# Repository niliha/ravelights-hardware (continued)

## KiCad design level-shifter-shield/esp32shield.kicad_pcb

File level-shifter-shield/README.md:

#  ESP32-DevKitC Level Shifter Shield

A shield for the ESP32-DevKitC allowing 3.3V to 5V/12V level shifting of 8 outputs, allowing to drive WS28XX LEDs at a distance of up to 50 meters.

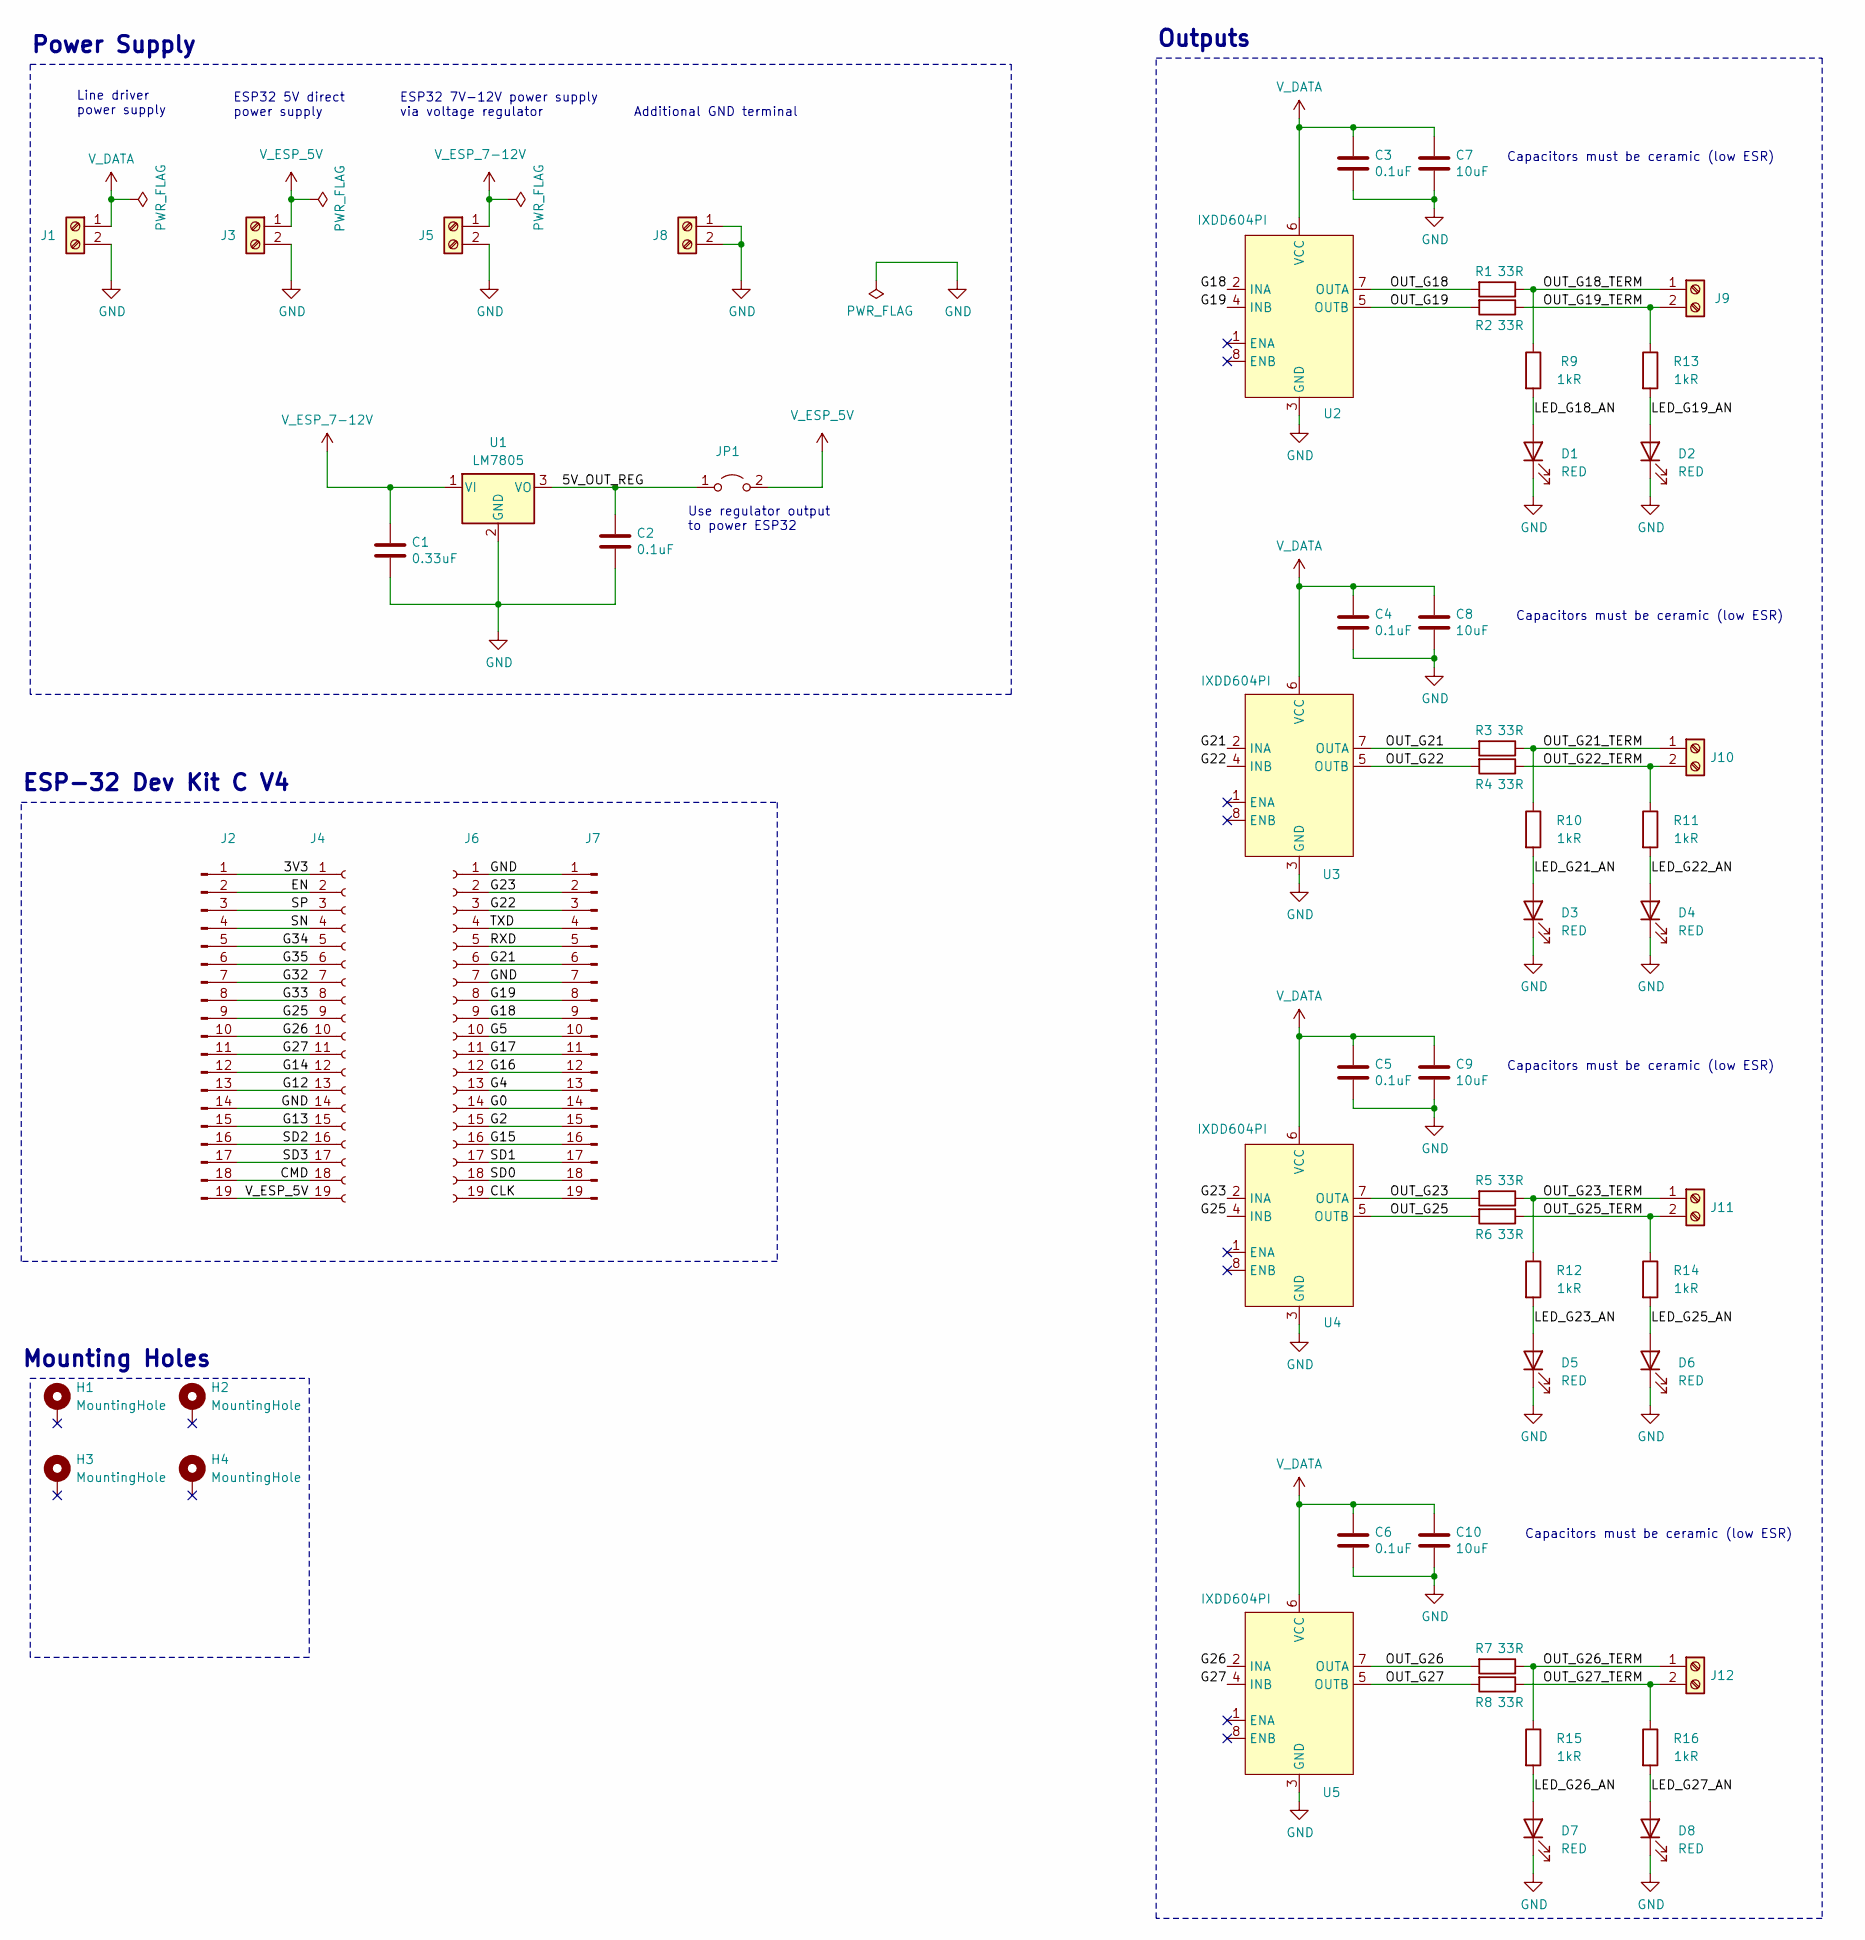
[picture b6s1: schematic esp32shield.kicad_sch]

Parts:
C1: 0.33uF; C_Disc_D3.0mm_W1.6mm_P2.50mm
C2, C3, C4, C5, C6: 0.1uF; C_Disc_D3.0mm_W1.6mm_P2.50mm
C7, C8, C9, C10: 10uF; C_Disc_D4.7mm_W2.5mm_P5.00mm
D1, D2, D3, D4, D5, D6, D7, D8: RED; LED_D3.0mm
H1, H2, H3, H4: MountingHole; MountingHole_2.2mm_M2_Pad
J1, J3, J5, J8: Power_Terminal; TerminalBlock_Phoenix_MKDS-1,5-2-5.08_1x02_P5.08mm_Horizont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
J2, J7: Conn_01x19_Pin; PinHeader_1x19_P2.54mm_Vertical
J4, J6: Conn_01x19_Socket; PinSocket_1x19_P2.54mm_Vertical
J9, J10, J11, J12: Screw_Terminal_01x02; TerminalBlock_Phoenix_MKDS-1,5-2-5.08_1x02_P5.08mm_Horizont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
JP1: Jumper_2_Open; PinHeader_1x02_P2.54mm_Vertical
R1, R2, R3, R4, R5, R6, R7, R8: 33R; R_Axial_DIN0207_L6.3mm_D2.5mm_P2.54mm_Vertical
R9, R10, R11, R12, R13, R14, R15, R16: 1kR; R_Axial_DIN0207_L6.3mm_D2.5mm_P2.54mm_Vertical
U1: LM7805; TO-220-3_Vertical
U2, U3, U4, U5: IXDD604PI; DIP-8_W7.62mm_Socket

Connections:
/3V3: J2.1, J4.1
/5V_OUT_REG: C2.1, JP1.1 (A), U1.3 (VO)
/CLK: J6.19, J7.19
/CMD: J2.18, J4.18
/EN: J2.2, J4.2
/G0: J6.14, J7.14
/G2: J6.15, J7.15
/G4: J6.13, J7.13
/G5: J6.10, J7.10
/G12: J2.13, J4.13
/G13: J2.15, J4.15
/G14: J2.12, J4.12
/G15: J6.16, J7.16
/G16: J6.12, J7.12
/G17: J6.11, J7.11
/G18: J6.9, J7.9, U2.2 (INA)
/G19: J6.8, J7.8, U2.4 (INB)
/G21: J6.6, J7.6, U3.2 (INA)
/G22: J6.3, J7.3, U3.4 (INB)
/G23: J6.2, J7.2, U4.2 (INA)
/G25: J2.9, J4.9, U4.4 (INB)
/G26: J2.10, J4.10, U5.2 (INA)
/G27: J2.11, J4.11, U5.4 (INB)
/G32: J2.7, J4.7
/G33: J2.8, J4.8
/G34: J2.5, J4.5
/G35: J2.6, J4.6
/LED_G18_AN: D1.2 (A), R9.2
/LED_G19_AN: D2.2 (A), R13.2
/LED_G21_AN: D3.2 (A), R10.2
/LED_G22_AN: D4.2 (A), R11.2
/LED_G23_AN: D5.2 (A), R12.2
/LED_G25_AN: D6.2 (A), R14.2
/LED_G26_AN: D7.2 (A), R15.2
/LED_G27_AN: D8.2 (A), R16.2
/OUT_G18: R1.2, U2.7 (OUTA)
/OUT_G18_TERM: J9.1, R1.1, R9.1
/OUT_G19: R2.2, U2.5 (OUTB)
/OUT_G19_TERM: J9.2, R2.1, R13.1
/OUT_G21: R3.2, U3.7 (OUTA)
/OUT_G21_TERM: J10.1, R3.1, R10.1
/OUT_G22: R4.2, U3.5 (OUTB)
/OUT_G22_TERM: J10.2, R4.1, R11.1
/OUT_G23: R5.2, U4.7 (OUTA)
/OUT_G23_TERM: J11.1, R5.1, R12.1
/OUT_G25: R6.2, U4.5 (OUTB)
/OUT_G25_TERM: J11.2, R6.1, R14.1
/OUT_G26: R7.2, U5.7 (OUTA)
/OUT_G26_TERM: J12.1, R7.1, R15.1
/OUT_G27: R8.2, U5.5 (OUTB)
/OUT_G27_TERM: J12.2, R8.1, R16.1
/RXD: J6.5, J7.5
/SD0: J6.18, J7.18
/SD1: J6.17, J7.17
/SD2: J2.16, J4.16
/SD3: J2.17, J4.17
/SN: J2.4, J4.4
/SP: J2.3, J4.3
/TXD: J6.4, J7.4
GND: C1.2, C2.2, C3.2, C4.2, C5.2, C6.2, C7.2, C8.2, C9.2, C10.2, D1.1 (K), D2.1 (K), D3.1 (K), D4.1 (K), D5.1 (K), D6.1 (K), D7.1 (K), D8.1 (K), J1.2, J2.14, J3.2, J4.14, J5.2, J6.1, J6.7, J7.1, J7.7, J8.1, J8.2, U1.2 (GND), U2.3 (GND), U3.3 (GND), U4.3 (GND), U5.3 (GND)
V_DATA: C3.1, C4.1, C5.1, C6.1, C7.1, C8.1, C9.1, C10.1, J1.1, U2.6 (VCC), U3.6 (VCC), U4.6 (VCC), U5.6 (VCC)
V_ESP_5V: J2.19, J3.1, J4.19, JP1.2 (B)
V_ESP_7-12V: C1.1, J5.1, U1.1 (VI)

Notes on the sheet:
Use regulator output to power ESP32
Additional GND terminal
Capacitors must be ceramic (low ESR)
Outputs
Line driver power supply
ESP32 7V-12V power supply via voltage regulator
ESP32 5V direct power supply
ESP-32 Dev Kit C V4
Power Supply
Mounting Holes

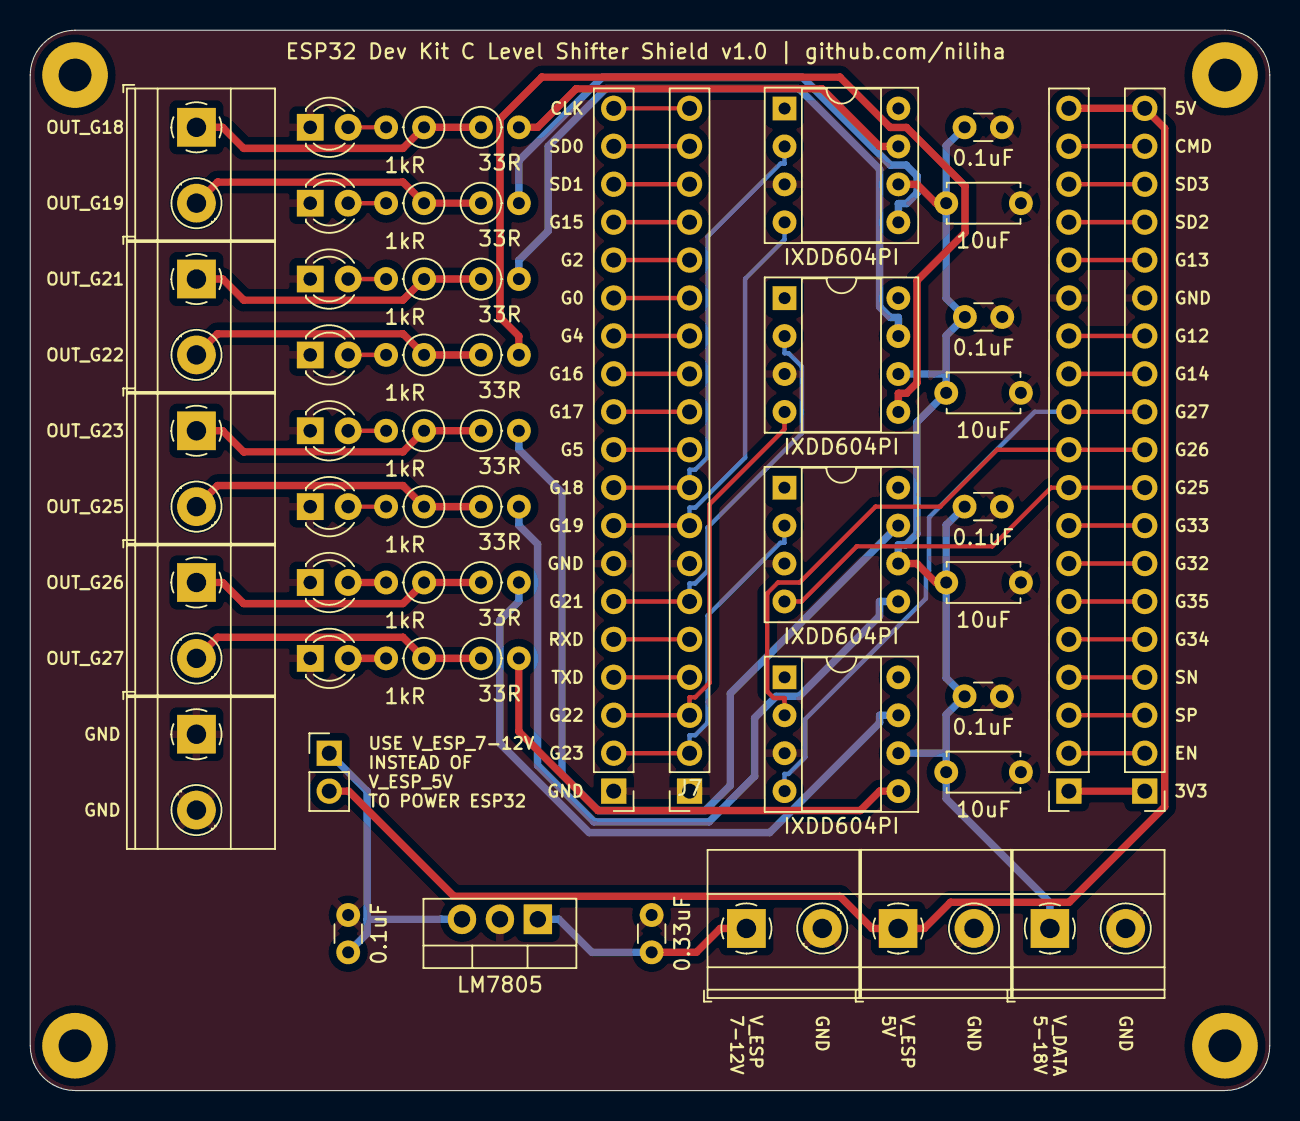
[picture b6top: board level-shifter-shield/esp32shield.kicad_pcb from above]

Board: 2 copper layers, 83.0 x 71.0 mm, 56 parts (0 on the bottom side), 63 nets.

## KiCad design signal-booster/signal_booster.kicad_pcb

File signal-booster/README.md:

# WS28XX Signal Booster

Allows to transmit up to 2 WS28XX data signals over long distances (up to 50m when GND and DATA are close together) while protecting the microcontroller pin or LED chip from sourcing too much current.
This PCB embeds an `IXDD604PI` gate driver IC acting as high-current line driver.
Further details can be derived from the [datasheet](https://ixapps.ixys.com/DataSheet/IXD_604.pdf).

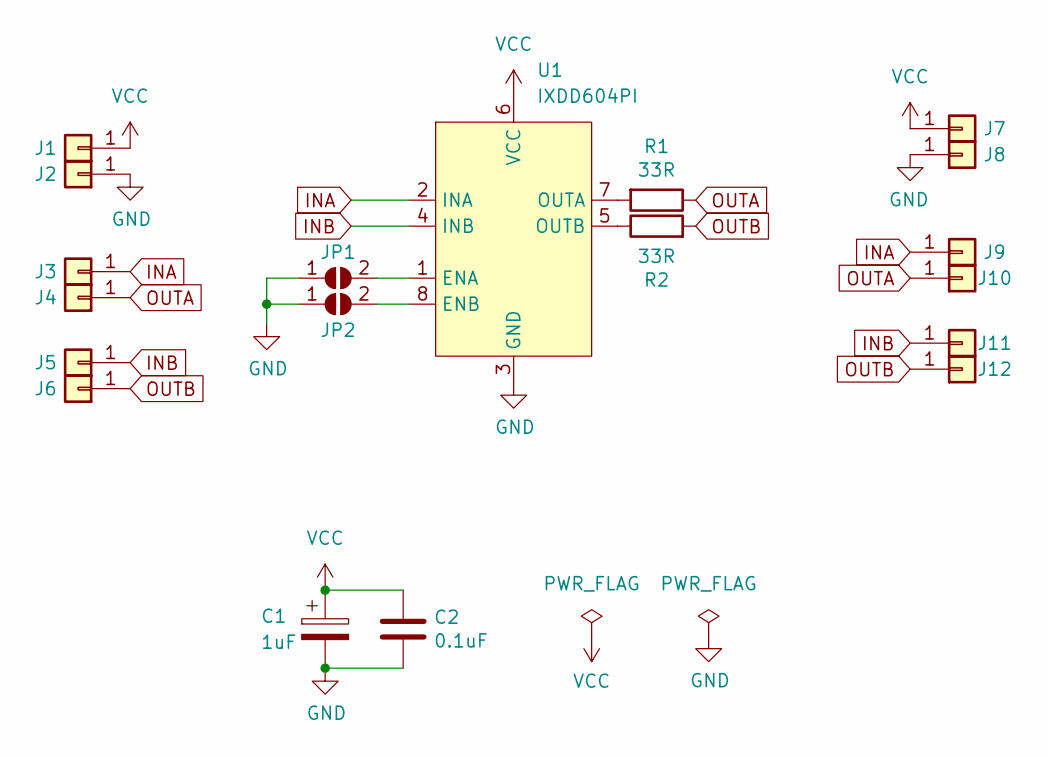
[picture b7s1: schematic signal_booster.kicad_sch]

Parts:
C1: 1uF; CP_Radial_D4.0mm_P2.00mm
C2: 0.1uF; C_Disc_D3.0mm_W1.6mm_P2.50mm
J1, J2, J3, J4, J5, J6, J7, J8, J9, J10, J11, J12: Conn_01x01; SolderWire-0.5sqmm_1x01_D0.9mm_OD2.1mm
JP1, JP2: SolderJumper_2_Open; SolderJumper-2_P1.3mm_Open_RoundedPad1.0x1.5mm
R1, R2: 33R; R_Axial_DIN0207_L6.3mm_D2.5mm_P2.54mm_Vertical
U1: IXDD604PI; DIP-8_W7.62mm_Socket

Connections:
GND: C1.2, C2.2, J2.1, J8.1, JP1.1 (A), JP2.1 (A), U1.3 (GND)
INA: J3.1, J9.1, U1.2 (INA)
INB: J5.1, J11.1, U1.4 (INB)
unnamed: JP1.2 (B), U1.1 (ENA)
unnamed: JP2.2 (B), U1.8 (ENB)
unnamed: R1.2, U1.7 (OUTA)
unnamed: R2.1, U1.5 (OUTB)
OUTA: J4.1, J10.1, R1.1
OUTB: J6.1, J12.1, R2.2
VCC: C1.1, C2.1, J1.1, J7.1, U1.6 (VCC)

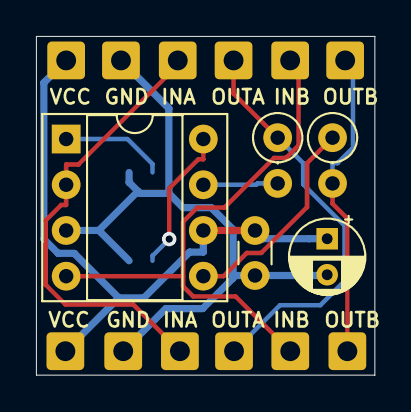
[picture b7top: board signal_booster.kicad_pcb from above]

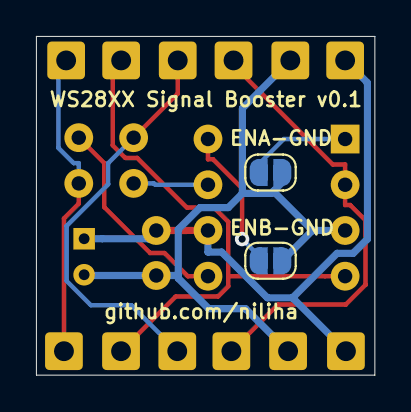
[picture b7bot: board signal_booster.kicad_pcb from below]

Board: 2 copper layers, 18.8 x 18.8 mm, 19 parts (2 on the bottom side), 10 nets.

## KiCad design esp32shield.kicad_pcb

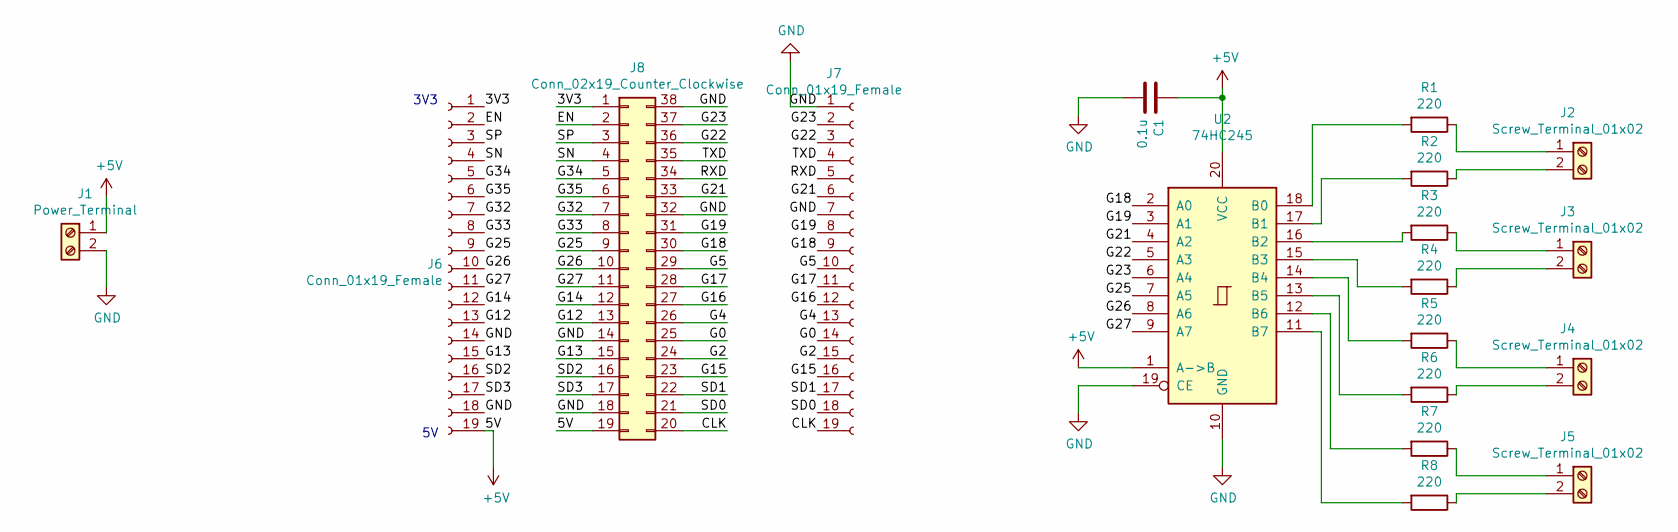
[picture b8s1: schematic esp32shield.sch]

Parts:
C1: 0.1u; C_Disc_D3.0mm_W1.6mm_P2.50mm
J1: Power_Terminal; TerminalBlock_Phoenix_MKDS-1,5-2_1x02_P5.00mm_Horizontal
J2, J3, J4, J5: Screw_Terminal_01x02; TerminalBlock_Phoenix_MKDS-1,5-2-5.08_1x02_P5.08mm_Horizont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
J6, J7: Conn_01x19_Female; PinSocket_1x19_P2.54mm_Vertical
J8: Conn_02x19_Counter_Clockwise; PinHeader_2x19_P2.54mm_Vertical
R1, R2, R3, R4, R5, R6, R7, R8: 220; R_Axial_DIN0207_L6.3mm_D2.5mm_P2.54mm_Vertical
U2: 74HC245; DIP-20_W7.62mm

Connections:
+5V: C1.1, J1.1, J6.19, J8.19, U2.1 (A->B), U2.20 (VCC)
/3V3: J6.1, J8.1
/CLK: J7.19, J8.20
/EN: J6.2, J8.2
/G0: J7.14, J8.25
/G2: J7.15, J8.24
/G4: J7.13, J8.26
/G5: J7.10, J8.29
/G12: J6.13, J8.13
/G13: J6.15, J8.15
/G14: J6.12, J8.12
/G15: J7.16, J8.23
/G16: J7.12, J8.27
/G17: J7.11, J8.28
/G18: J7.9, J8.30, U2.2 (A0)
/G19: J7.8, J8.31, U2.3 (A1)
/G21: J7.6, J8.33, U2.4 (A2)
/G22: J7.3, J8.36, U2.5 (A3)
/G23: J7.2, J8.37, U2.6 (A4)
/G25: J6.9, J8.9, U2.7 (A5)
/G26: J6.10, J8.10, U2.8 (A6)
/G27: J6.11, J8.11, U2.9 (A7)
/G32: J6.7, J8.7
/G33: J6.8, J8.8
/G34: J6.5, J8.5
/G35: J6.6, J8.6
/RXD: J7.5, J8.34
/SD0: J7.18, J8.21
/SD1: J7.17, J8.22
/SD2: J6.16, J8.16
/SD3: J6.17, J8.17
/SN: J6.4, J8.4
/SP: J6.3, J8.3
/TXD: J7.4, J8.35
GND: C1.2, J1.2, J6.14, J6.18, J7.1, J7.7, J8.14, J8.18, J8.32, J8.38, U2.10 (GND), U2.19 (CE)
unnamed: J2.1, R1.1
unnamed: J2.2, R2.1
unnamed: J3.1, R3.1
unnamed: J3.2, R4.1
unnamed: J4.1, R5.1
unnamed: J4.2, R6.1
unnamed: J5.1, R7.1
unnamed: J5.2, R8.1
unnamed: R1.2, U2.18 (B0)
unnamed: R2.2, U2.17 (B1)
unnamed: R3.2, U2.16 (B2)
unnamed: R4.2, U2.15 (B3)
unnamed: R5.2, U2.14 (B4)
unnamed: R6.2, U2.13 (B5)
unnamed: R7.2, U2.12 (B6)
unnamed: R8.2, U2.11 (B7)

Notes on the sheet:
3V3

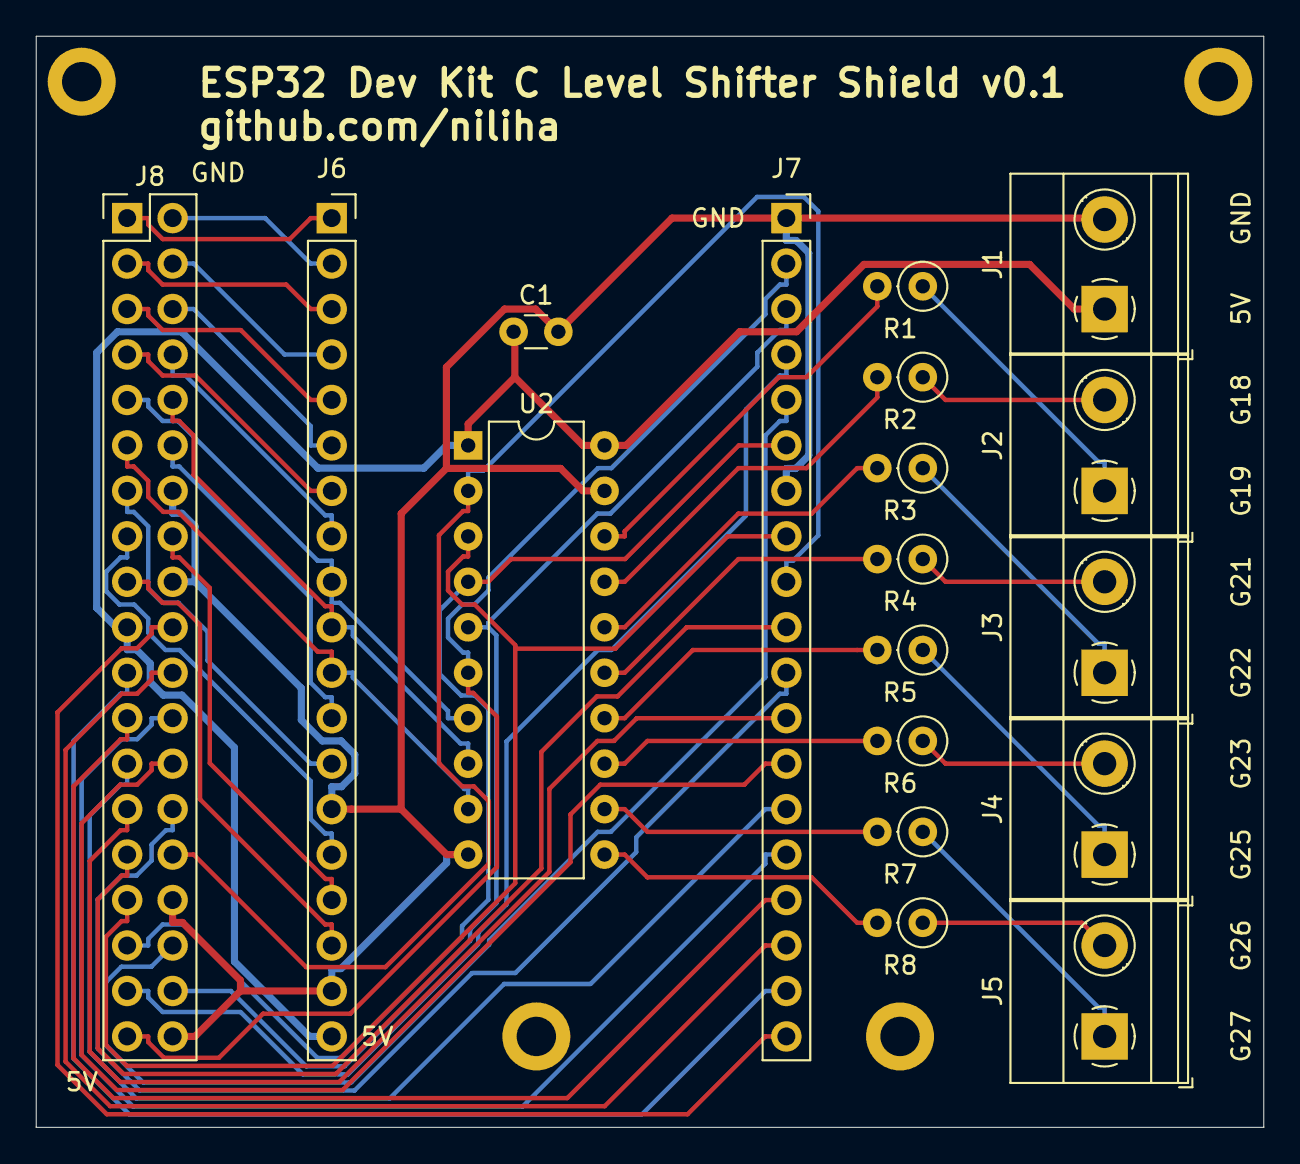
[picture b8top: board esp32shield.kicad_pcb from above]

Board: 2 copper layers, 68.6 x 61.0 mm, 22 parts (0 on the bottom side), 51 nets.

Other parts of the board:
H1, H2, H3, H4: MountingHole_2.2mm_M2_DIN965_Pad

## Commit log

2022-03-30 Add version v0.1
2023-11-05 Add schematic for signal booster
2023-11-06 Add layout for signal booster
2023-11-07 Generate gerber files
2023-12-17 Create README.md for signal booster
2023-12-27 Finish new level shifter shield schematic
2024-01-03 Finish level shifter shield layout without traces
2024-01-07 Adapt level shifter shield layout and add routing
2024-02-01 Add production files for level shifter shield
2024-02-03 Finish AC dimmer schematic
2024-02-04 Dimmer: Assign footprints
2024-02-04 [WIP] Layout AC dimmer
2024-02-04 Finish AC dimmer layout and add production files
2024-02-04 Finish AC dimmer driver
2024-02-05 Route 230V traces
2024-02-05 Finish manual re-routing
2024-02-13 Create production files for ac dimmer
2024-02-13 Rename projects
2024-03-23 Add 8-channel leading edge AC dimmer project
2024-03-23 Clean up repository
2024-03-23 Add SPI port expander schematic
2024-03-24 Finish SPI port expander layout
2024-03-24 Create production files for SPI port expander
2024-03-24 Create README.md for SPI port expander
2024-03-24 Create README.md for leading edge AC dimmer
2024-09-03 Add README for trailing edge AC dimmer
2024-09-04 Update README of leading edge dimmer
2024-09-04 Update README for trailing edge dimmer
2025-09-04 Add schematic for DC PWM dimmer
2025-09-13 Add power routing
2025-09-13 Optimize base routing
2025-09-13 Finish routing
2025-10-11 Finalize DC dimmer v0.1
2025-10-11 Begin with improving dc dimmer
